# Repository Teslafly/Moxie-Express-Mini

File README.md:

# Moxie-Express-Mini
A version of the VESC Express in a very small footprint using JST GH connectors and adds some extended functionality

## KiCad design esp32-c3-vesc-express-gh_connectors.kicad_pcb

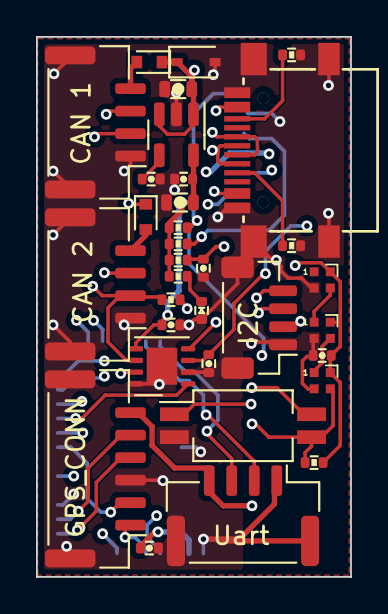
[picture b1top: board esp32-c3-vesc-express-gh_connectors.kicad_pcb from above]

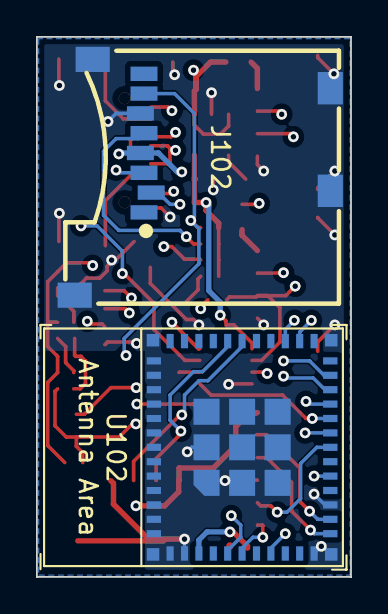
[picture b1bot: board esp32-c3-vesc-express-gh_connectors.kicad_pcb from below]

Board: 4 copper layers, 17.4 x 30.0 mm, 35 parts (2 on the bottom side), 31 nets.

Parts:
C101, C104: 10uF; C_0603
C102: 0.1uF; C_0402
C103, C105, C106, C107, C108, C201: 2.2uF; C_0402
D101, D102: D; D_SOD-523
D103: BLUE; D_0402
D104: 5V TVS; D_SOD-323
D105, D106, D107: SK6805; LED_SK6812_EC15_1.5x1.5mm
J101: GPS_CONN; JST_GH_BM06B-GHS-TBT_1x06-1MP_P1.25mm_Vertical
J102: Micro_SD_Card; TF-SMD_TF-05
J301: USB_C_Receptacle_USB2.0; USB-C-SMD_YTC-TC16S-26-A
P101: CAN 1; JST_GH_BM04B-GHS-TBT_1x04-1MP_P1.25mm_Vertical
P102: CAN 2; JST_GH_BM04B-GHS-TBT_1x04-1MP_P1.25mm_Vertical
P103: Uart; JST_GH_BM04B-GHS-TBT_1x04-1MP_P1.25mm_Vertical
P104: I2C; JST_SH_BM04B-SRSS-TB_1x04-1MP_P1.00mm_Vertical
R101: 220Ω; R_0402
R102, R103, R104, R105, R106, R301, R302: 5.1kΩ; R_0402
SW101: SW_DIP_x02; SW_DIP_SPSTx02_Slide_Copal_CHS-02B_W7.62mm_P1.27mm
U101: AP2210K-3.3TRG1; SOT-23-5
U102: ESP32-C3-MINI-1
U201: TJA1051T-3; DFN-8-1EP_3x3mm_P0.65mm_EP1.7x2.05mm

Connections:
+3V3: C103.1, C104.1, C106.2, C107.2, C108.2, D105.4 (VDD), D106.4 (VDD), D107.4 (VDD), J102.4 (VDD), P104.2, R102.2, R103.1, R104.1, R105.1, R106.1, U101.5 (VOUT), U102.3 (3V3), U201.5 (VIO)
+5V: C101.1, C201.1, D101.1 (K), D102.1 (K), D104.1 (A1), J101.6, P103.4, U101.1 (VIN), U101.3 (ON/~OFF), U201.3 (VCC)
/BOOT/GPIO9: D105.3 (DIN), R105.2, SW101.3, U102.23 (GPIO9)
/CAN1_5V_D: D101.2 (A), P101.4
/CAN2_5V_D: D102.2 (A), P102.4
/CAN_R: R101.2, SW101.4
/CAN_RX: U102.19 (GPIO5/ADC2_CH0), U201.4 (RXD)
/CAN_TX: U102.20 (GPIO6), U201.1 (TXD)
/CAN_tranciever/CANH: P101.3, P102.3, SW101.1, U201.7 (CANH)
/CAN_tranciever/CANL: P101.2, P102.2, R101.1, U201.6 (CANL)
/ESC_UART_RX: P103.3, U102.31 (GPIO21/U0TXD)
/ESC_UART_TX: P103.2, U102.30 (GPIO20/U0RXD)
/ESP32_EN: C105.2, R106.2, U102.8 (EN/CHIP_PU)
/GPS_BOOT/SCL: J101.1, P104.4, U102.6 (GPIO3/ADC1_CH3)
/GPS_PPS/SDA: J101.2, P104.3, U102.18 (GPIO4/ADC1_CH4)
/GPS_UART_RX: J101.5, U102.13 (GPIO1/ADC1_CH1/XTAL_32K_N)
/GPS_UART_TX: J101.4, U102.12 (GPIO0/ADC1_CH0/XTAL_32K_P)
/LED_BL_R: D103.C, R102.1
/SD_CS: J102.2 (DAT3/CD), U102.16 (GPIO10)
/SD_MISO: J102.7 (DAT0), R104.2, U102.5 (GPIO2/ADC1_CH2)
/SD_MOSI: J102.3 (CMD), U102.21 (GPIO7)
/SD_SCK: J102.5 (CLK), R103.2, U102.22 (GPIO8)
/USB connector/USB_CC1: J301.A5 (CC1), R302.2
/USB connector/USB_CC2: J301.B5 (CC2), R301.2
/USB_DM: J301.A7 (D-), J301.B7 (D-), U102.27 (GPIO19/USB_D+)
/USB_DP: J301.A6 (D+), J301.B6 (D+), U102.26 (GPIO18/USB_D-)
/led_d1: D105.1 (DOUT), D106.3 (DIN)
/led_d2: D106.1 (DOUT), D107.3 (DIN)
GND: C101.2, C102.2, C103.2, C104.2, C105.1, C106.1, C107.1, C108.1, C201.2, D103.A, D104.2 (A2), D105.2 (VSS), D106.2 (VSS), D107.2 (VSS), J101.3, J101.MP (MountPin), J102.6 (VSS), J102.9 (SHIELD), J301.A1 (GND), J301.A12 (GND), J301.S1 (SHIELD), P101.1, P101.MP (MountPin), P102.1, P102.MP (MountPin), P103.1, P103.MP (MountPin), P104.1, P104.MP (MountPin), R301.1, R302.1, SW101.2, U101.2 (GND), U102.1 (GND), U102.2 (GND), U102.11 (GND), U102.14 (GND), U102.36 (GND), U201.2 (GND), U201.8 (S), U201.9 (PAD)
unnamed: C102.1, U101.4 (BP)
USB_VBUS: J301.A4 (VBUS), J301.A9 (VBUS)

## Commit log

2023-03-10 initial commit of v1 board
2023-03-10 remove some extra files
